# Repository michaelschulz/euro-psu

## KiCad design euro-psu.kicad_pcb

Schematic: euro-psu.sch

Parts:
C1, C5: CP; CP_Radial_D17.0mm_P7.50mm
C2, C6: CP; CP_Radial_D10.0mm_P5.00mm
C3, C7: C; C_Disc_D6.0mm_W4.4mm_P5.00mm
C4, C8: CP; CP_Radial_D5.0mm_P2.50mm
D1, D2, D3, D4, D5, D6, D7: 1N4004; D_A-405_P7.62mm_Horizontal
H1: PIN_HEADER_2x8; IDC-Header_2x08_P2.54mm_Vertical
J1: Screw_Terminal_01x04; TerminalBlock_TE_282834-4_1x04_P2.54mm_Horizontal
U1: LM7912_TO220; TO-220-3_Vertical
U2: LM7812; TO-220-3_Vertical
U3: LM7805_TO220; TO-220-3_Vertical

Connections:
Earth: J1.2
GND: C1.2, C2.2, C3.2, C4.2, C5.1, C6.1, C7.2, C8.1, H1.4, H1.6, H1.8, J1.3, U1.1 (GND), U2.2 (GND_2), U3.2
unnamed: C1.1, C2.1, C3.1, D2.1 (K), D4.1 (K), D5.1 (K), D7.1 (K), U2.1 (VI_1), U3.1
unnamed: C4.1, D5.2 (A), H1.10, U2.3 (VO_3)
unnamed: C5.2, C6.2, C7.1, D1.2 (A), D3.2 (A), D6.2 (A), U1.2 (VI)
unnamed: C8.2, D6.1 (K), H1.2, U1.3 (VO)
unnamed: D1.1 (K), D2.2 (A), J1.4
unnamed: D3.1 (K), D4.2 (A), J1.1
unnamed: D7.2 (A), H1.12, U3.3

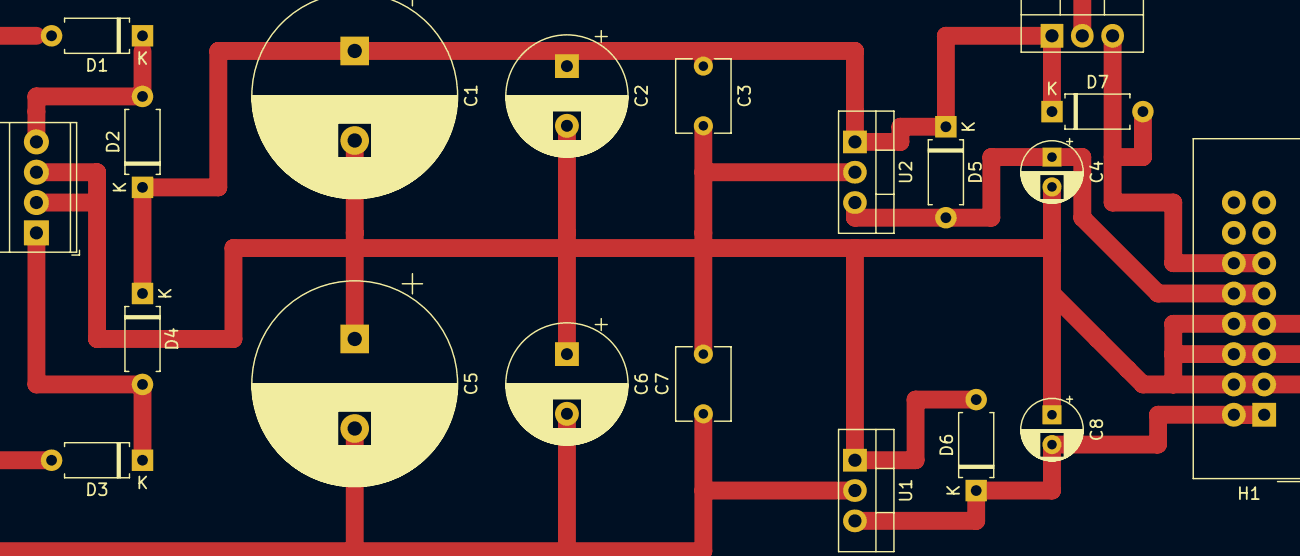
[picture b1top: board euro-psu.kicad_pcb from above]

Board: 2 copper layers, 20 parts (0 on the bottom side), 8 nets.
